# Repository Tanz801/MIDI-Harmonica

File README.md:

This is a midi controller in the form of a harmonica. This was made for week 3 of Hack Club's half life, where the theme was to make an instrument. Chose to make a harmonica at the suggestion of a friend.

## Features
10 holes each with their own air pressure sensor
Joystick for pitch bends
Vibrato button
Pitch shift buttons
slider for texture selection

## PCB

## Flashing firmware

to be done

## Assmebling

to be done

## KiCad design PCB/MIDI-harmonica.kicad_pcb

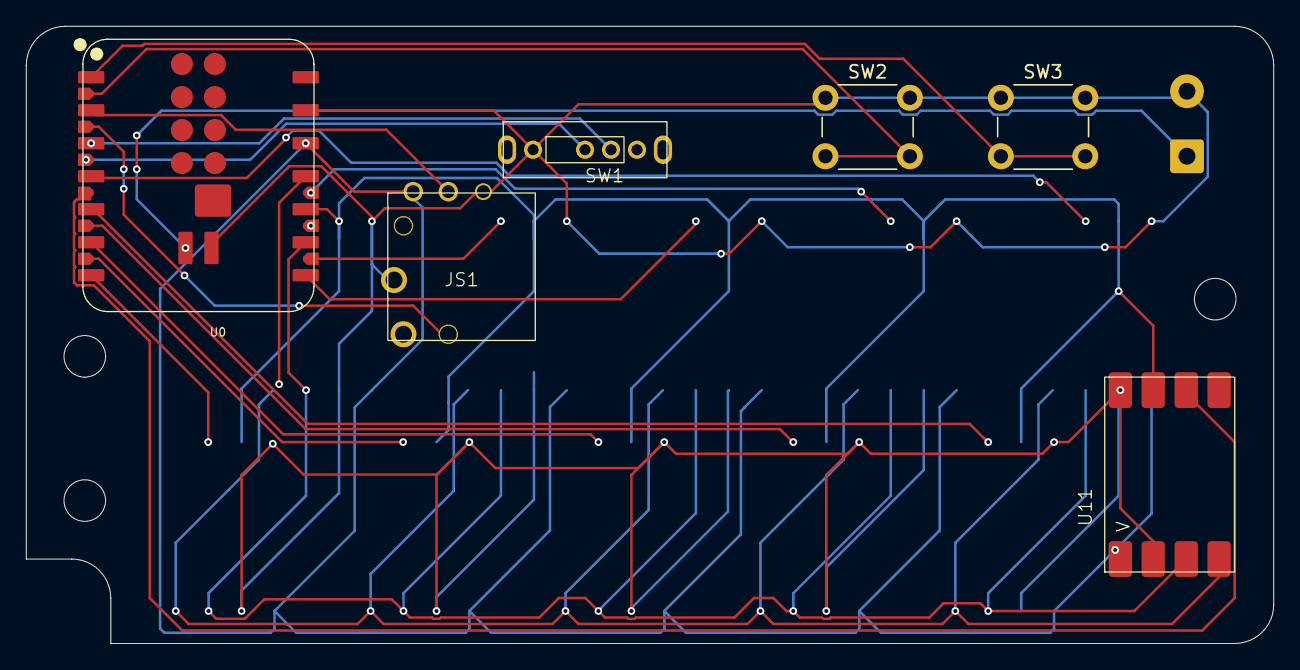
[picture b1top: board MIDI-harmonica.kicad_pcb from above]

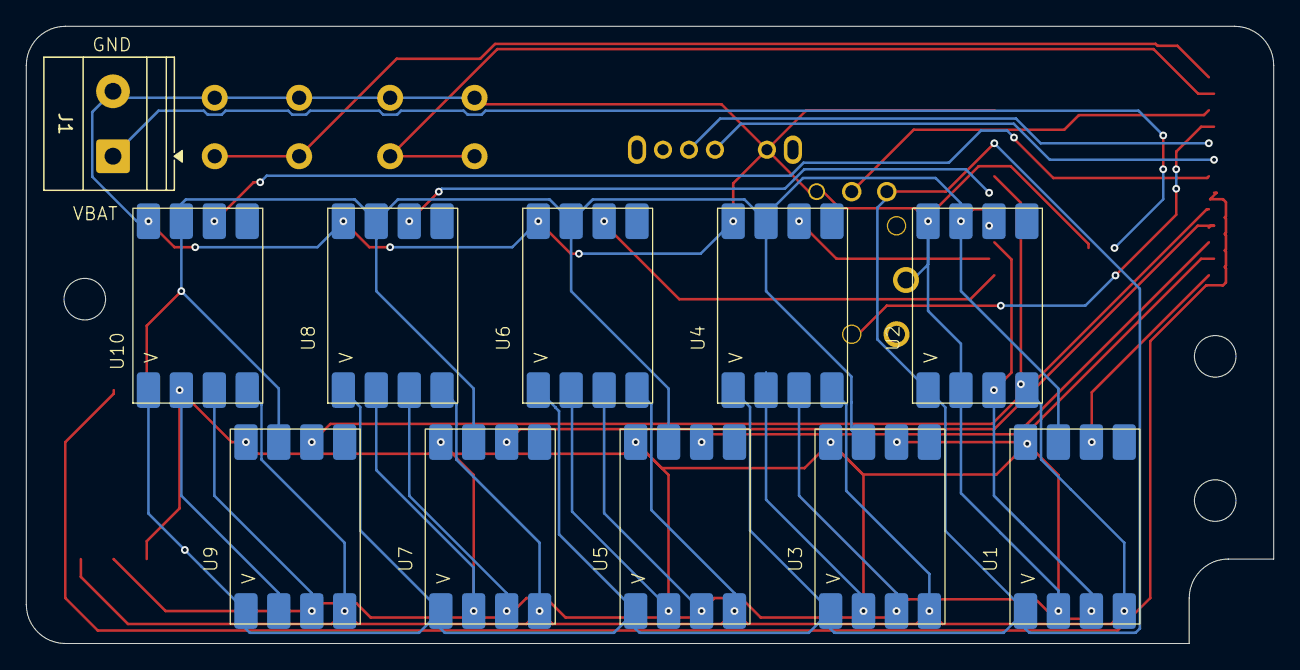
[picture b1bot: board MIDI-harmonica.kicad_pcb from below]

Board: 2 copper layers, 96.0 x 47.5 mm, 17 parts (11 on the bottom side), 23 nets.

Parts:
J1: Screw_Terminal_01x02; TerminalBlock_Phoenix_MKDS-1,5-2_1x02_P5.00mm_Horizontal
JS1: FJ06K
SW1: SW_SP3T; SS13D07
SW2, SW3: SW_Push; SW_PUSH_6mm
U0: XIAO-ESP32-S3-Plus-SMD
U1, U2, U3, U4, U5, U6, U7, U8, U9, U10, U11: BMP580

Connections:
+3.3V: JS1.1, U0.12 (3V3_OUT), U1.1 (VCC), U2.1 (VCC), U3.1 (VCC), U4.1 (VCC), U5.1 (VCC), U6.1 (VCC), U7.1 (VCC), U8.1 (VCC), U9.1 (VCC), U10.1 (VCC), U11.1 (VCC)
+BATT: J1.1, U0.32 (VBAT)
/CLK: U0.9 (D8), U1.3 (SCL), U2.3 (SCL), U3.3 (SCL), U4.3 (SCL), U5.3 (SCL), U6.3 (SCL), U7.3 (SCL), U8.3 (SCL), U9.3 (SCL), U10.3 (SCL), U11.3 (SCL)
/SDI: U0.11 (D10), U1.4 (SDA), U2.4 (SDA), U3.4 (SDA), U4.4 (SDA), U5.4 (SDA), U6.4 (SDA), U7.4 (SDA), U8.4 (SDA), U9.4 (SDA), U10.4 (SDA), U11.4 (SDA)
/SDO: U0.10 (D9), U1.6 (SDO), U2.6 (SDO), U3.6 (SDO), U4.6 (SDO), U5.6 (SDO), U6.6 (SDO), U7.6 (SDO), U8.6 (SDO), U9.6 (SDO), U10.6 (SDO), U11.6 (SDO)
/U1: U0.7 (D6), U1.7 (CS)
/U2: U0.22 (D18), U2.7 (CS)
/U3: U0.20 (D16), U3.7 (CS)
/U4: U0.21 (D19), U4.7 (CS)
/U5: U0.6 (D5), U5.7 (CS)
/U6: U0.8 (D7), U6.7 (CS)
/U7: U0.19 (D15), U7.7 (CS)
/U8: U0.23 (D17), U8.7 (CS)
/U9: U0.5 (D4), U9.7 (CS)
/U10: U0.4 (D3), U10.7 (CS)
/U11: U0.18 (D14), U11.7 (CS)
/add: SW2.2, U0.15 (D11)
/analogX: JS1.2, U0.2 (D1)
/joystick_sw: JS1.8 (SW2), U0.16 (D12)
/mono: SW1.2, U0.17 (D13)
/poly: SW1.3, U0.3 (D2)
/subtract: SW3.2, U0.1 (D0)
GND: J1.2, JS1.3, JS1.7 (SW1), SW1.1, SW2.1, SW3.1, U0.13 (GND), U0.33 (GND), U1.2 (GND), U1.5 (GND), U2.2 (GND), U2.5 (GND), U3.2 (GND), U3.5 (GND), U4.2 (GND), U4.5 (GND), U5.2 (GND), U5.5 (GND), U6.2 (GND), U6.5 (GND), U7.2 (GND), U7.5 (GND), U8.2 (GND), U8.5 (GND), U9.2 (GND), U9.5 (GND), U10.2 (GND), U10.5 (GND), U11.2 (GND), U11.5 (GND)

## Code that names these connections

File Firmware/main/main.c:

#include <stdio.h>
#include "driver/gpio.h"

const gpio_num_t CLK = 7;
const gpio_num_t SDO = 8;
const gpio_num_t SDI = 9;

const gpio_num_t add = 38;
const gpio_num_t subtract = 1;
const gpio_num_t vibrato = 39;

void app_main(void)
{

}
